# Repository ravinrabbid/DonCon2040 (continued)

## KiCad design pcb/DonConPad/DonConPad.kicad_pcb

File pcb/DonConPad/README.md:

# DonConPad - A Simple I2C Gamepad with Display

This board breaks out an MCP23017 I/O expander to some conveniently placed push buttons and offers a spot for an SSD1306 OLED display.
Both I/O expander and display are connected to the same i2c bus.

The i2c address for the MCP23017 can be configured using the jumpers JP1, JP2 and JP3, which are pulled down to GND when open.

## Case

A 3D-printable case can be found in the [case subdirectory](./Case/). Print the `Top`, the `Bottom` and 14 `Buttons`. Insert 6mm diameter M4 heat set inserts into the top part and screw together using M4 screws.  

## Bill of Materials

| **Reference**          |       **Description**       |       **Digikey Part**       |                                 **Notes**                                 |
| ---------------------- | :-------------------------: | :--------------------------: | :-----------------------------------------------------------------------: |
| J1                     | SSD1306 OLED Display Module |              -               | Dimension wise 128x64 or 128x32 should fit. Make sure the pinout matches. |
| J2                     |  5Pin S5B-PH-K-S Connector  |         455-1722-ND          | PHR-5 plus SPH-002T-P0.5L is the counterpart                              |
| U1                     |    MCP23017 IO Expander     |       MCP23017-E/SO-ND       |                                                                           |
| SW1-14                 |    6x6mm Tactile Switch     | e.g. TS02-66-60-BK-100-LCR-D |                                                                           |
| C1                     | 0.1µF SMD Ceramic Capacitor |        1276-1003-1-ND        |                                                                           |
| C2                     | 10µF SMD Ceramic Capacitor  |        1276-6454-1-ND        |                                                                           |
| R1, R2, R3, R4, R5, R6 |      10kΩ SMD Resistor      |  2019-RK73H2ATTD1002FCT-ND   |                                                                           |

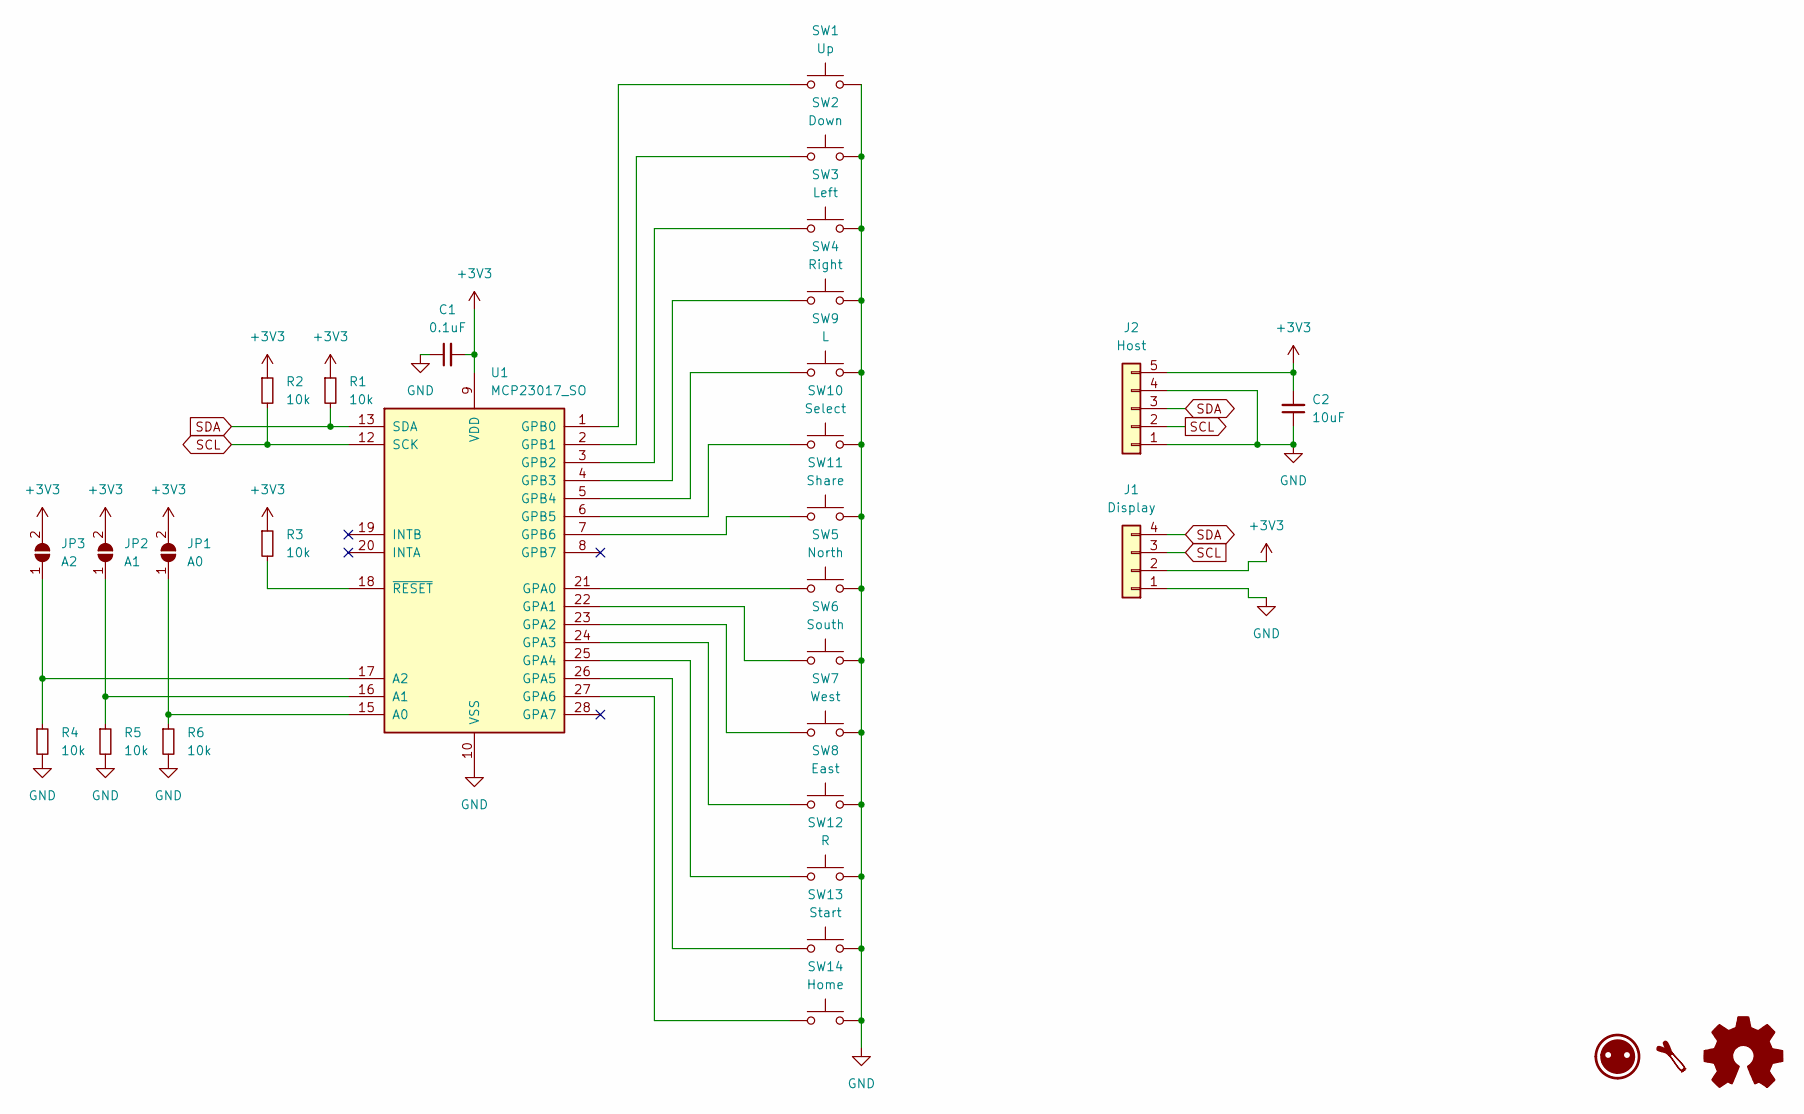
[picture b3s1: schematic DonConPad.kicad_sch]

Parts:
C1: 0.1uF; C_0805_2012Metric_Pad1.18x1.45mm_HandSolder
C2: 10uF; C_0805_2012Metric_Pad1.18x1.45mm_HandSolder
J1: Display; PinHeader_1x04_P2.54mm_Vertical
J2: Host; JST_PH_S5B-PH-K_1x05_P2.00mm_Horizontal
JP1: A0; SolderJumper-2_P1.3mm_Open_TrianglePad1.0x1.5mm
JP2: A1; SolderJumper-2_P1.3mm_Open_TrianglePad1.0x1.5mm
JP3: A2; SolderJumper-2_P1.3mm_Open_TrianglePad1.0x1.5mm
R1, R2, R3, R4, R5, R6: 10k; R_0805_2012Metric_Pad1.20x1.40mm_HandSolder
SW1: Up; SW_PUSH_6mm_H5mm
SW2: Down; SW_PUSH_6mm_H5mm
SW3: Left; SW_PUSH_6mm_H5mm
SW4: Right; SW_PUSH_6mm_H5mm
SW5: North; SW_PUSH_6mm_H5mm
SW6: South; SW_PUSH_6mm_H5mm
SW7: West; SW_PUSH_6mm_H5mm
SW8: East; SW_PUSH_6mm_H5mm
SW9: L; SW_PUSH_6mm_H5mm
SW10: Select; SW_PUSH_6mm_H5mm
SW11: Share; SW_PUSH_6mm_H5mm
SW12: R; SW_PUSH_6mm_H5mm
SW13: Start; SW_PUSH_6mm_H5mm
SW14: Home; SW_PUSH_6mm_H5mm
U1: MCP23017_SO; SOIC-28W_7.5x17.9mm_P1.27mm

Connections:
+3V3: C1.2, C2.2, J1.2, J2.5, JP1.2 (B), JP2.2 (B), JP3.2 (B), R1.1, R2.1, R3.1, U1.9 (VDD)
GND: C1.1, C2.1, J1.1, J2.1, J2.4, R4.2, R5.2, R6.2, SW1.2, SW2.2, SW3.2, SW4.2, SW5.2, SW6.2, SW7.2, SW8.2, SW9.2, SW10.2, SW11.2, SW12.2, SW13.2, SW14.2, U1.10 (VSS)
unnamed: JP1.1 (A), R6.1, U1.15 (A0)
unnamed: JP2.1 (A), R5.1, U1.16 (A1)
unnamed: JP3.1 (A), R4.1, U1.17 (A2)
unnamed: SW5.1, U1.21 (GPA0)
unnamed: SW6.1, U1.22 (GPA1)
unnamed: SW7.1, U1.23 (GPA2)
unnamed: SW8.1, U1.24 (GPA3)
unnamed: SW12.1, U1.25 (GPA4)
unnamed: SW13.1, U1.26 (GPA5)
unnamed: SW14.1, U1.27 (GPA6)
unnamed: SW1.1, U1.1 (GPB0)
unnamed: SW2.1, U1.2 (GPB1)
unnamed: SW3.1, U1.3 (GPB2)
unnamed: SW4.1, U1.4 (GPB3)
unnamed: SW9.1, U1.5 (GPB4)
unnamed: SW10.1, U1.6 (GPB5)
unnamed: SW11.1, U1.7 (GPB6)
unnamed: R3.2, U1.18 (~RESET)
SCL: J1.3, J2.2, R2.2, U1.12 (SCK)
SDA: J1.4, J2.3, R1.2, U1.13 (SDA)

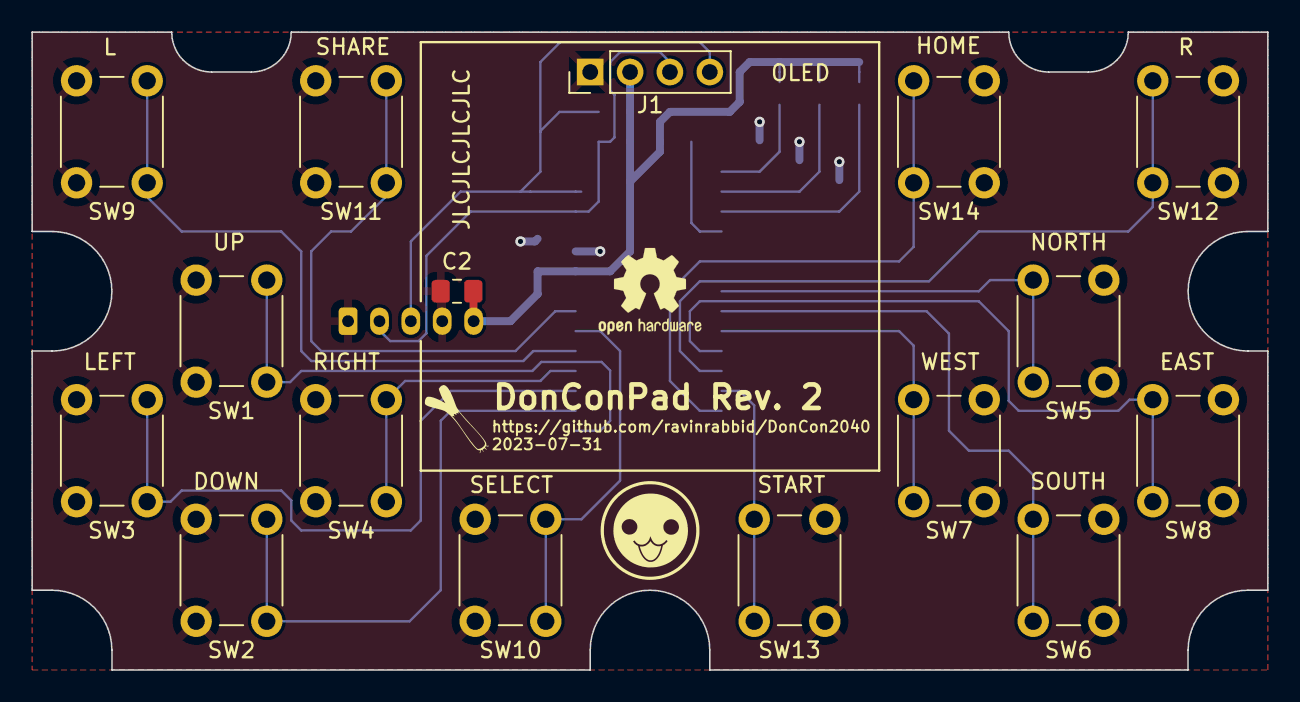
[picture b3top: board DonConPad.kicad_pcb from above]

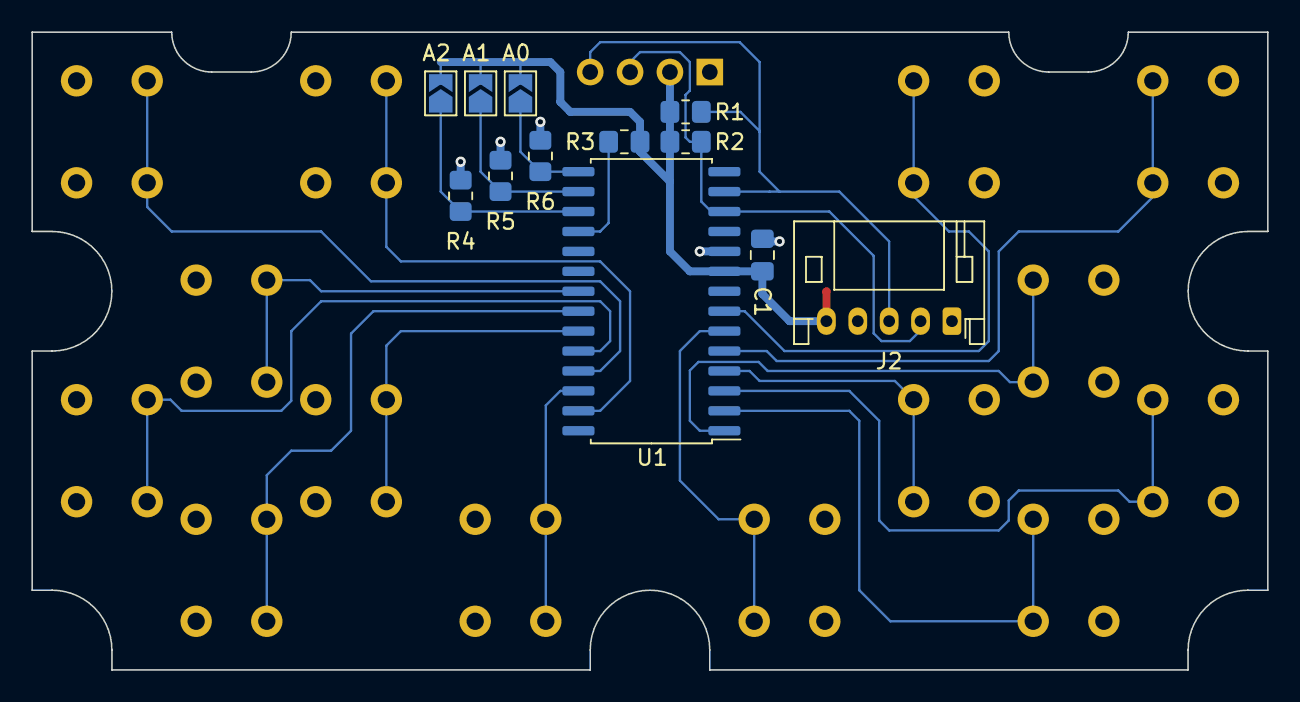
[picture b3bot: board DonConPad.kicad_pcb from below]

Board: 2 copper layers, 78.7 x 40.6 mm, 31 parts (12 on the bottom side), 22 nets.

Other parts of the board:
LOGO1: OSHW-Logo2_7.3x6mm_SilkScreen
LOGO2: LOGO; Leek-Logo_6.3mm_Silkscreen
LOGO3: Donchan-Logo_6.3mm_Silkscreen

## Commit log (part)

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2023-04-10 Initial skeleton
2023-04-10 Add drum pad input handling
2023-04-22 Add status led to show current input state
2023-04-22 Switch to tinyUsb stack
2023-04-22 Add xinput driver
2023-05-13 Rework Drum to use ADC inputs
2023-05-20 Implement library for MCP23017 IO expander
2023-05-20 Add support for additional controller buttons
2023-05-20 Reverse polarity on IO expander
    This is to avoid false inputs if controllers is disconnected.
2023-05-21 Move controller input to second core
2023-05-21 Add ssd1306 display driver
2023-07-01 Draw Idle Screen
2023-07-02 Remove hardest hit detection again
2023-07-04 Port over the remaining USB modes from DivaCon
2023-07-05 Add usb mode to GlobalConfiguration
2023-07-05 Add IO Board Schematic
2023-07-06 Add persistent settings store
    In preparation for on-screen menu.
2023-07-06 Add menu backend
2023-07-09 Adjust menu button assignments
2023-07-09 Draw basic menu on screen
2023-07-09 Fix: LED Brightness not configurable
2023-07-16 Add basic roll counters
2023-07-16 Change some resistor values to improve sensitivity
2023-07-16 Scale thresholds for hard hits
    To avoid false inputs on neighboring pads for very hard hits,
    thresholds can now be scaled dynamically according to the highest
    input.
    This is controlled by the trigger_threshold_scale_level, ranging
    from 0 for no scaling to 255 for max scaling. Mind that the scaling
    is non-linear and changes in the higher end of the value range have
2023-07-16 Add trigger threshold level to settings store
2023-07-16 Add Menu Backgrounds
2023-07-16 Add on-screen configuration for thresholds
2023-07-16 Add settings reset via on-screen menu
2023-07-17 Add MIDI device mode
2023-07-22 Add README for IO Board
2023-07-22 Add README
2023-07-27 Add external ADC to DonConIO PCB
2023-08-01 Add library for MCP3204 ADC
2023-08-05 Add PCB for external gamepad
2023-08-05 Add missing level shifter to IO board
2023-08-08 Support Pairing Data Report 0x12
    Some hosts, i.e. newer linux kernels, use this to get the device MAC
2023-08-09 Export IO board schematic pdf
2023-08-09 Update IO Board Readme
2023-08-09 Add support for external ADC
2023-08-09 Export Pad schematic to pdf
2023-08-09 Add DonConPad Readme
2023-08-11 Fix: Setting Ka Right sensitivty via menu
2023-08-12 Fix: Add missing settings in GlobalConfiguration.h
2023-08-12 Set Buttons Pins to match DonConPad PCB
2023-11-05 Make menu navigation stack based
2023-11-25 Make debounce delay configurable via on-screen menu
2023-11-26 Rework DS4 structs based on linux kernel hid driver
2023-12-02 Fix Debounce delay on-screen menu
2023-12-02 Release buttons when entering menu
2023-12-03 Add Keyboard Mode
2023-12-03 Reword Debounce Delay to Hold Time
2023-12-03 Simplify false hit detection
    For now, only allow one input at a time
2023-12-03 Support DS4 Plater Color on LED
2023-12-03 Calculate Roll Counte on core0
2023-12-29 Display previous roll below roll counter
2023-12-29 Add Second Keyboard mode
    There a now two keyboard modes to easily allow two players on the
    same computer. Player 1 is mapped to 'DFJK', player 2 to 'CBN,'.
2024-10-12 Allow left+right double hits
    The largest reading for each side is taken into account.
2024-10-12 Add XInput Analog mode
    This mode will map the readouts of the drum to the left (for player 1)
    or right (for player 2) analogstick axis.
2024-11-07 Rework Menu
    - Live preview of all settings
    - Settings will be applied with 'Select/Apply' or reset with 'Back'
    - DS4 player color can be en-/disabled
2024-11-07 Refactor USB drivers
2024-11-07 Simplify status LED color mixing
2024-11-13 Use DMA for reading external ADC
    The external ADC will constantly convert, reading will give
    the maximum value since the last read. This should avoid
    missing any peaks.
    The internal ADC will now only do one conversion upon read,
    consider it abandoned for now.
2024-11-13 Fix menu buttons for toggle options
2024-11-13 Rework README
2024-11-16 Improve PS4 compatibility
    PS4 Tatacon will be recognized by PS4, but will timeout after
    around 8 minutes like all unauthorized controllers.
    Dualshock4 mode will not work on PS4.
2024-11-16 Fix Dualshock 3 Emulation
    Missing reports were added and it will now work on an actual PS3.
2024-11-24 Add 3d printable case for DonConPad
2024-11-24 Further improve hit detection
    - Already consider thresholds when searching strongest hit
    - Only allow either DON or KA to be triggered
    - Only count hits on both sides when within 50% of each other
2024-11-24 Switch back to raw values for debug mode
2024-11-24 Add hint for sensitivity tuning in DonConIO README
2024-11-24 Take debounce state into account for input filter
2024-12-01 Fix wrong assignment for left/right buttons in value settings
2024-12-01 Refactor ADC configuration
2025-04-18 Add controller authentication support for PS4
    This avoid the 8 minute timeout on PS4 if the
    according files are provided.
2025-04-18 Increase clock rate to 200MHz
    This comes with an update to pico-sdk 2.1.1
2025-06-28 Fix trigger thresholds capped at 255
    Thresholds can now be configured up to 4095.
2025-07-13 Add DonConIOmini PCB
2025-07-13 Adjust default config for DonConIOmini
2025-07-19 Add support for internal GPIOs
    The controller can now also be configured to use internal GPIO pins
    instead of an external IO expander.
2025-07-20 Fix setting threshold values larger than 255
2025-08-27 Add fast repeat for setting values in menu
    After holding a button for 5 seconds the value change rate in menus
    will become even faster to make setting large values less of a
    hassle.
2025-08-27 Add Double Trigger feature
    Double Trigger can be configured to
    - 'Off'
    For the previous behaviour
    - 'Threshold' (with a separate set of thresholds)
    For triggering both sides if a pad is hit harder than the double
    trigger threshold
2025-09-26 clang-tidy: Set enum sizes
2025-09-26 clang-tidy: Fix include guards
2025-09-26 Switch to C++20
2025-09-28 clang-tidy: modernize
2025-09-28 Refactor Mcp3204Dma
2025-09-28 clangt-tidy mc23017 library
2025-09-28 clang-tidy: performance and readability
2025-09-28 clang-tidy: cppcoreguidelines
2025-09-28 Add configuration for legacy DonConIO board
2025-09-28 Refactor InputState
2025-09-28 ws2812_pio: Properly latch led data
2025-09-28 clang-tidy: bugprone
2025-09-28 clang-tidy: misc
2025-09-28 refactor: remove static variables in members
2025-09-28 clang-tidy: Fix clang diagnostics
2026-04-21 DonConPad README: add missing 5-pin JST-PH connector to the BoM
    Same part, Digi-Key part number and comment as the corresponding
    connector (J5) of DonConIOmini.
2026-04-21 DonConIOmini README: swap DK part numbers for C17 and C18/C19
    Previously they were the other way around.
2026-04-21 DonConIOmini README: remove no-longer-needed capacitors from the BoM
2026-05-19 Fix build for RP2350
2026-05-19 Show 'busy' hint while signing auth challenge
2026-05-19 Update READMEs regarding RP2350
2026-05-29 Add support to emulate Wii TaTaCon
2026-05-29 clang-tidy
2026-05-29 Add idle timeout for wii extension mode
2026-05-31 Dynamically assign ws2812 statemachine
2026-05-31 clang-tidy libs
2026-06-01 Add support to emulate PS2 TaTaCon
2026-06-04 Add missing deinit functions in device drivers
2026-06-26 Fix Debug build not booting
    stdio_init_all() must be called after tud_init() otherwise asserts false.
